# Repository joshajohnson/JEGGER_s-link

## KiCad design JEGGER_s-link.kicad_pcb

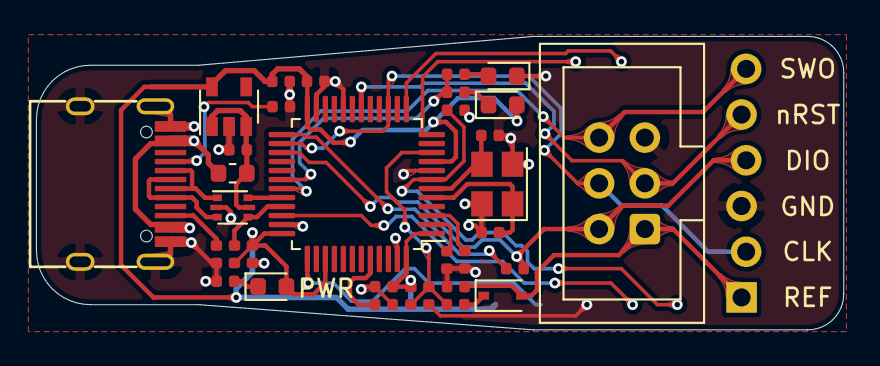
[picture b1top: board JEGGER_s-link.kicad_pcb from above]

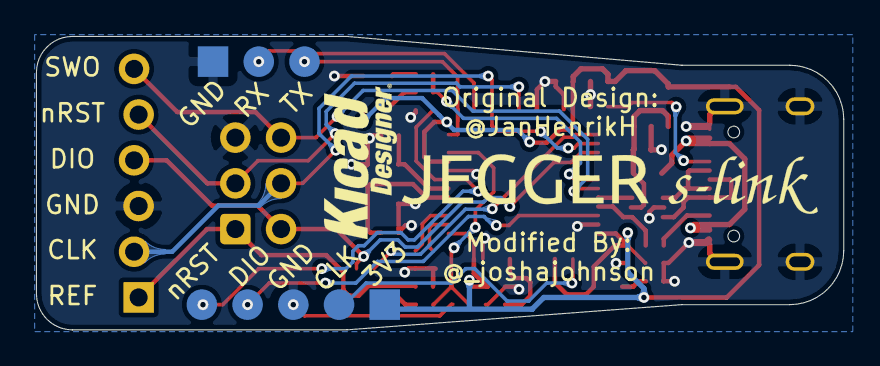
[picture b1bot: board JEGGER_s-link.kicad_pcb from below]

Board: 2 copper layers, 44.8 x 16.3 mm, 36 parts (2 on the bottom side), 32 nets.

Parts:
C1, C2: 1u; C_0402_1005Metric
C3, C4: 22p; C_0402_1005Metric
C5, C6, C7, C8: 100n; C_0402_1005Metric
D1: GREEN; LED_0603_1608Metric
D2: RED; LED_0603_1608Metric
D3: BAT60JFILM; D_SOD-323
D4: PWR; LED_0603_1608Metric
F1: 500mA; Fuse_0603_1608Metric
J1: USB; USB_C_U262-161N-4BVC11
J2: Tag-Connect; IDC-Header_2x03_P2.54mm_Vertical
J3: STM_DEBUG; STM_5_PIN_SMD_PROG
J4: OUT; STM_6_PIN_THT_Staggered
J5: STLINK_UART; UART_3_PIN_SMD_PROG
R1: 10K; R_0402_1005Metric
R2, R3, R5, R6, R7, R9, R10, R11, R12, R13: 5K1; R_0402_1005Metric
R4, R8: 100R; R_0402_1005Metric
R14: 1K5; R_0402_1005Metric
U1: USBLC6-2P6; SOT-666
U2: AP2112K-3.3; SOT-23-5
U3: STM32F103CBTx; LQFP-48_7x7mm_P0.5mm
Y1: 8Mhz; Crystal_SMD_3225-4Pin_3.2x2.5mm

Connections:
+3V3: C2.1, C6.2, C7.2, C8.2, D1.2, D4.2, J3.1, R12.1, R14.1, U2.5, U3.1, U3.9, U3.24, U3.36, U3.39, U3.48
/A_IN: R4.2, R12.2, R13.1, U3.10
/D+: R14.2, U1.4, U3.33
/D-: U1.6, U3.32
/LED_STLINK: R2.1, R3.2, U3.30
/STLINK_RX: J5.2, U3.13
/STLINK_TX: J5.3, U3.12
/STM_JTCK: J3.2, U3.37
/STM_JTMS: J3.4, U3.34
/STM_nRST: C5.2, J3.5, U3.7
/T_JTCK: J2.4, J4.2, U3.15, U3.26
/T_JTMS: J2.2, J4.4, R8.1, U3.27
/T_SWDIO_IN: R8.2, U3.25
/T_SWO: J2.6, J4.6, U3.31
/T_nRST: J2.3, J4.5, U3.18
/USB_D+: J1.A6, J1.B6, U1.3
/USB_D-: J1.A7, J1.B7, U1.1
/V_REF: D3.2, J2.1, J4.1, R1.2
GND: C1.2, C2.2, C3.1, C4.2, C5.1, C6.1, C7.1, C8.1, D2.1, J1.A1, J1.A12, J1.B1, J1.B12, J1.S1, J2.5, J3.3, J4.3, J5.1, R1.1, R5.1, R6.1, R7.2, R9.2, R10.2, R11.2, R13.2, U1.2, U2.2, U3.8, U3.20, U3.23, U3.35, U3.47, Y1.2, Y1.4
unnamed: C3.2, U3.5, Y1.1
unnamed: C4.1, U3.6, Y1.3
unnamed: D1.1, R2.2
unnamed: D2.2, R3.1
unnamed: D3.1, R4.1
unnamed: D4.1, R7.1
unnamed: F1.2, J1.A4, J1.A9, J1.B4, J1.B9
unnamed: J1.A5, R5.2
unnamed: J1.B5, R6.2
unnamed: R9.1, U3.2
unnamed: R10.1, U3.3
unnamed: R11.1, U3.44
VBUS: C1.1, F1.1, U1.5, U2.1, U2.3

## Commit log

2020-05-23 changed schematic
2020-05-23 layout done
2020-05-23 added silk
2020-05-23 generated gerbers
